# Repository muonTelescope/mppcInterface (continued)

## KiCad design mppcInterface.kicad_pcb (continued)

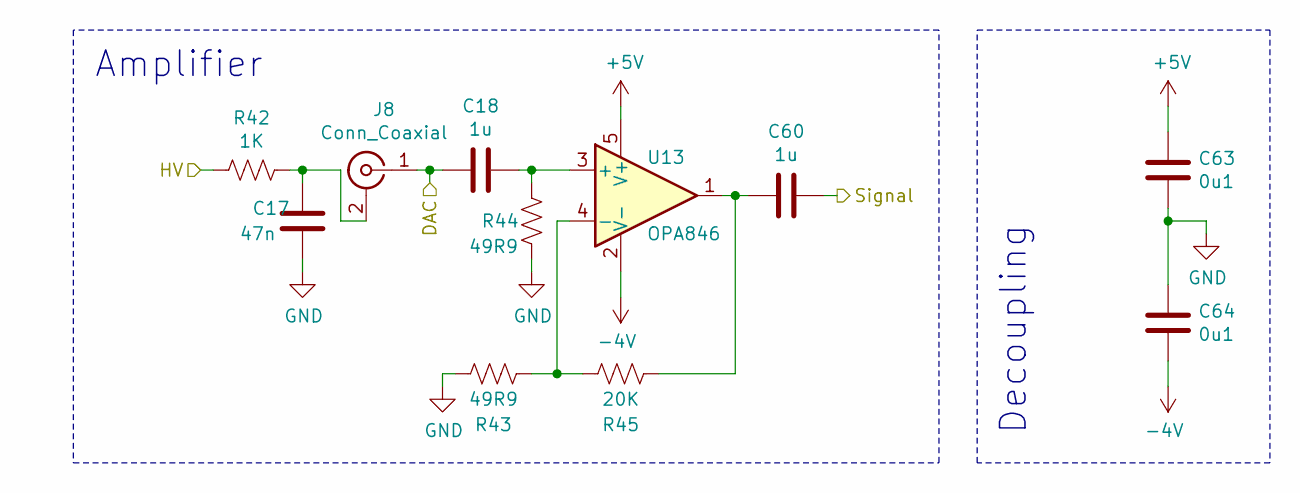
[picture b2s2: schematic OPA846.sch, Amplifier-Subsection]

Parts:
C3: 47n; C_0402_1005Metric
C4, C25: 1u; C_0402_1005Metric
C28, C29: 0u1; C_0402_1005Metric
J1: Conn_Coaxial; U.FL_Hirose_U.FL-R-SMT-1_Vertical
R7: 1K; R_0402_1005Metric
R8, R9: 49R9; R_0402_1005Metric
R10: 20K; R_0402_1005Metric
U6: OPA846; SOT-23-5

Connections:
+5V: C28.1, U6.5 (V+); also elsewhere on the board
-4V: C29.2, U6.2 (V-); also elsewhere on the board
/DAC0: C4.2, J1.1 (In); also elsewhere on the board
/HV: R7.2; also elsewhere on the board
CH0: C25.1; also elsewhere on the board
GND: C3.2, C28.2, C29.1, R8.1, R9.1; also elsewhere on the board
unnamed: C3.1, J1.2 (Ext), R7.1
unnamed: C4.1, R9.2, U6.3 (+)
unnamed: C25.2, R10.1, U6.1
unnamed: R8.2, R10.2, U6.4 (-)

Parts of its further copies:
C5, C7, C9, C11, C13, C15, C17: 47n; C_0402_1005Metric
C6, C8, C10, C12, C14, C16, C18, C30, C35, C40, C45, C50, C55, C60: 1u; C_0402_1005Metric
C33, C34, C38, C39, C43, C44, C48, C49, C53, C54, C58, C59, C63, C64: 0u1; C_0402_1005Metric
J2, J3, J4, J5, J6, J7, J8: Conn_Coaxial; U.FL_Hirose_U.FL-R-SMT-1_Vertical
R12, R17, R22, R27, R32, R37, R42: 1K; R_0402_1005Metric
R13, R14, R18, R19, R23, R24, R28, R29, R33, R34, R38, R39, R43, R44: 49R9; R_0402_1005Metric
R15, R20, R25, R30, R35, R40, R45: 20K; R_0402_1005Metric
U7, U8, U9, U10, U11, U12, U13: OPA846; SOT-23-5

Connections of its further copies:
+5V: C33.1, C38.1, C43.1, C48.1, C53.1, C58.1, C63.1, U7.5 (V+), U8.5 (V+), U9.5 (V+), U10.5 (V+), U11.5 (V+), U12.5 (V+), U13.5 (V+); also elsewhere on the board
-4V: C34.2, C39.2, C44.2, C49.2, C54.2, C59.2, C64.2, U7.2 (V-), U8.2 (V-), U9.2 (V-), U10.2 (V-), U11.2 (V-), U12.2 (V-), U13.2 (V-); also elsewhere on the board
/DAC1: C6.2, J2.1 (In); also elsewhere on the board
/DAC2: C8.2, J3.1 (In); also elsewhere on the board
/DAC3: C10.2, J4.1 (In); also elsewhere on the board
/DAC4: C12.2, J5.1 (In); also elsewhere on the board
/DAC5: C14.2, J6.1 (In); also elsewhere on the board
/DAC6: C16.2, J7.1 (In); also elsewhere on the board
/DAC7: C18.2, J8.1 (In); also elsewhere on the board
/HV: R12.2, R17.2, R22.2, R27.2, R32.2, R37.2, R42.2; also elsewhere on the board
CH1: C30.1; also elsewhere on the board
CH2: C35.1; also elsewhere on the board
CH3: C40.1; also elsewhere on the board
CH4: C45.1; also elsewhere on the board
CH5: C50.1; also elsewhere on the board
CH6: C55.1; also elsewhere on the board
CH7: C60.1; also elsewhere on the board
GND: C5.2, C7.2, C9.2, C11.2, C13.2, C15.2, C17.2, C33.2, C34.1, C38.2, C39.1, C43.2, C44.1, C48.2, C49.1, C53.2, C54.1, C58.2, C59.1, C63.2, C64.1, R13.1, R14.1, R18.1, R19.1, R23.1, R24.1, R28.1, R29.1, R33.1, R34.1, R38.1, R39.1, R43.1, R44.1; also elsewhere on the board
unnamed: C5.1, J2.2 (Ext), R12.1
unnamed: C6.1, R14.2, U7.3 (+)
unnamed: C7.1, J3.2 (Ext), R17.1
unnamed: C8.1, R19.2, U8.3 (+)
unnamed: C9.1, J4.2 (Ext), R22.1
unnamed: C10.1, R24.2, U9.3 (+)
unnamed: C11.1, J5.2 (Ext), R27.1
unnamed: C12.1, R29.2, U10.3 (+)
unnamed: C13.1, J6.2 (Ext), R32.1
unnamed: C14.1, R34.2, U11.3 (+)
unnamed: C15.1, J7.2 (Ext), R37.1
unnamed: C16.1, R39.2, U12.3 (+)
unnamed: C17.1, J8.2 (Ext), R42.1
unnamed: C18.1, R44.2, U13.3 (+)
unnamed: C30.2, R15.1, U7.1
unnamed: C35.2, R20.1, U8.1
unnamed: C40.2, R25.1, U9.1
unnamed: C45.2, R30.1, U10.1
unnamed: C50.2, R35.1, U11.1
unnamed: C55.2, R40.1, U12.1
unnamed: C60.2, R45.1, U13.1
unnamed: R13.2, R15.2, U7.4 (-)
unnamed: R18.2, R20.2, U8.4 (-)
unnamed: R23.2, R25.2, U9.4 (-)
unnamed: R28.2, R30.2, U10.4 (-)
unnamed: R33.2, R35.2, U11.4 (-)
unnamed: R38.2, R40.2, U12.4 (-)
unnamed: R43.2, R45.2, U13.4 (-)

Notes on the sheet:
Decoupling
Amplifier

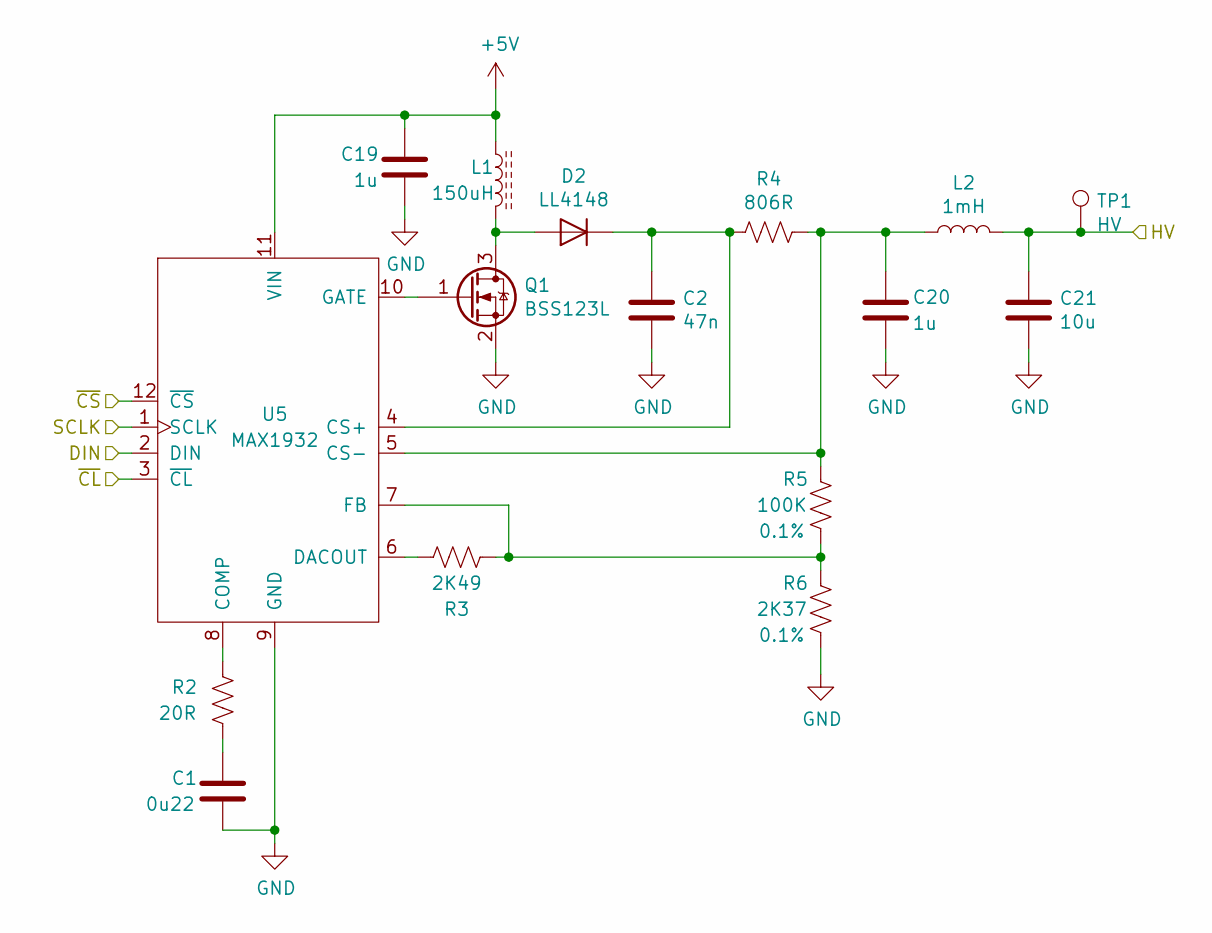
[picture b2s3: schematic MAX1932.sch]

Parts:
C1: 0u22; C_0402_1005Metric
C2: 47n; C_1206_3216Metric
C19: 1u; C_0805_2012Metric
C20: 1u; C_1206_3216Metric
C21: 10u; C_2220_5650Metric
D2: LL4148; D_MiniMELF
L1: 150uH; SRN4018
L2: 1mH; L_1210_3225Metric
Q1: BSS123L; SOT-23
R2: 20R; R_0402_1005Metric
R3: 2K49; R_0402_1005Metric
R4: 806R; R_0402_1005Metric
R5: 100K; R_0402_1005Metric; Tolerance 0.1%
R6: 2K37; R_0402_1005Metric; Tolerance 0.1%
TP1: HV; TestPoint_Bridge_Pitch2.0mm_Drill0.7mm
U5: MAX1932; TQFN-12

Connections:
+5V: C19.1, L1.1, U5.11 (VIN); also elsewhere on the board
/HV: C21.1, L2.2, TP1.1; also elsewhere on the board
CL: U5.3 (~CL)
GND: C1.2, C2.2, C19.2, C20.2, C21.2, Q1.2 (S), R6.2, U5.9 (GND); also elsewhere on the board
HV_CS: U5.12 (~CS); also elsewhere on the board
MOSI: U5.2 (DIN); also elsewhere on the board
unnamed: C1.1, R2.2
unnamed: C2.1, D2.1 (K), R4.2, U5.4 (CS+)
unnamed: C20.1, L2.1, R4.1, R5.1, U5.5 (CS-)
unnamed: D2.2 (A), L1.2, Q1.3 (D)
unnamed: Q1.1 (G), U5.10 (GATE)
unnamed: R2.1, U5.8 (COMP)
unnamed: R3.1, R5.2, R6.1, U5.7 (FB)
unnamed: R3.2, U5.6 (DACOUT)
SCLK: U5.1 (SCLK); also elsewhere on the board

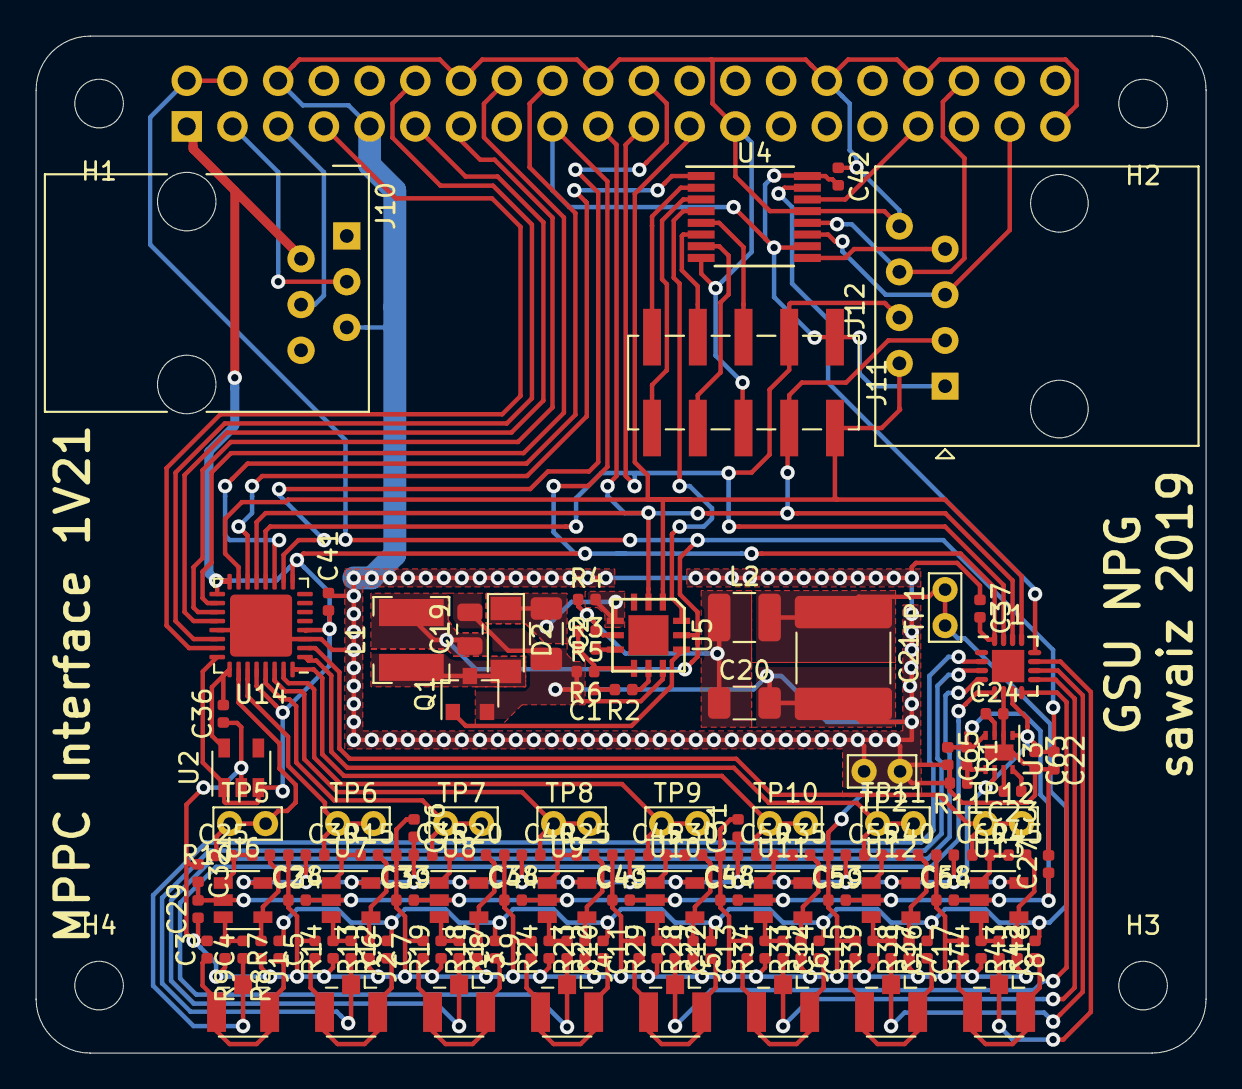
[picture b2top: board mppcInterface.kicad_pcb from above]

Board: 2 copper layers, 65.0 x 56.5 mm, 140 parts (1 on the bottom side), 90 nets.

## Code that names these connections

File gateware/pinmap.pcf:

# example.pcf

# Channels as inputs

set_io --warn-no-port CH0 31
set_io --warn-no-port CH1 32
set_io --warn-no-port CH2 1
set_io --warn-no-port CH3 2
set_io --warn-no-port CH4 20
set_io --warn-no-port CH5 22
set_io --warn-no-port CH6 23
set_io --warn-no-port CH7 26

set_io --warn-no-port LED0 30
set_io --warn-no-port LED1 29
set_io --warn-no-port LED2 27

# Output to Pi

set_io --warn-no-port gpioSDO 13 # Pin 13 is SDI on FPGA -> Pin 19, GPIO10, WiringPi 12, MOSI on RaspberryPi
set_io --warn-no-port gpioSDI 12 # Pin 12 is SDO on FPGA -> Pin 21, GPIO09, WiringPi 13, MISO on RaspberryPi
set_io --warn-no-port gpioSCK 15 # Pin 15 is SCK on FPGA -> Pin 23, GPIO11, WiringPi 14, SCK  on RaspberryPi
set_io --warn-no-port gpioSS  14 # Pin 14 is SS  on FPGA -> Pin 18, GPIO24, WiringPi 05, SS   on RaspberryPi

set_io --warn-no-port CLK     6  # Pin 6  on FPGA -> Pin 07, GPIO4, WiringPi 07, CLK on RaspberryPi

set_io --warn-no-port gpio18  7  # Pin 07 on FPGA -> Pin 12, GPIO18, WiringPi 01 on RaspberryPi 
set_io --warn-no-port gpio17  5  # Pin 05 on FPGA -> Pin 11, GPIO17, WiringPi 00 on RaspberryPi
set_io --warn-no-port gpio23  19 # Pin 19 on FPGA -> Pin 16, GPIO23, WiringPi 04 on RaspberryPi
set_io --warn-no-port gpio27  8  # Pin 08 on FPGA -> Pin 13, GPIO27, WiringPi 02 on RaspberryPi

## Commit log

2016-03-27 Copied over from other repo
2016-03-27 fdsfs
2016-04-06 Cad model Built
2016-04-22 Code has website and nodejs gpio control
2016-04-23 Website is coming along, code looks a lot better
2016-05-19 Removed code directory
2016-06-28 Changed to channel modules, still need a uC on board
2016-06-28 Schematic Changes
2016-06-29 Modules, Eth jack, and uC in place
2016-06-30 New step files, board outline added
2016-07-01 New Design
2016-07-05 updated assembly
2016-07-05 added 403C part
2016-07-05 Stuff
2016-07-05 Jonathan Doesnt Know How To Linux
2016-07-05 Routed Interface
2016-07-05 More Traces
2016-07-06 Arduino Traces Started
2016-07-06 Finished Traces
2016-07-06 Power and GND to board out
2016-07-07 Copper Pours and step/decal files
2016-07-07 Fixed Switch
2016-07-07 master slave traces
2016-07-08 Removing showcase files
2016-07-08 Added proper Readme
2016-07-08 Updated Submodule
2016-07-08 Change links to local refrences
2016-07-08 Updated BOM
2016-07-11 Added desktop.ini to gitIgnore
2016-07-12 updated assemblies
2016-07-12 updated decal
2016-07-12 updated board
2016-07-12 added I2C traces
2016-07-18 changed board
2016-07-19 updated renderings
2016-07-21 changed renderings
2016-07-21 changed a rendering
2016-07-22 Finished routing board
2016-07-25 Finished Board
2016-07-25 fixed board hole
2016-07-25 board thickness
2016-07-25 created 4 channel assembly
2016-07-25 Fixed BOM
2016-07-25 added pictures
2016-07-29 readme change
2016-07-29 added direct signal traces
2016-08-03 updated parts
2016-08-08 updated with new HV Boards
2016-08-09 added standoffs and updated assembly
2016-08-26 Updated Board for new voltage inverter and I2C LLC
2016-09-30 Updated version and renamed
2016-10-04 Renaming
2016-10-06 Ground plane fixes
2016-10-13 Smaller board, more compact routing
2016-10-13 Coincidence left
2016-10-17 Neg supply built
2016-10-18 Boad completed ready for review
2016-10-19 Cad completed, needs logo, name, and accelerometer
2016-10-19 Added logos, accelerometer, name, etc
2016-10-19 Replaced decals
2016-10-24 Added grounding pads, test pounts, fixed arduino master i2c swap
2016-10-25 marked V2, cad layout still left, uploaded to oshpark
2017-01-07 Updated to 2017 inventor files, redid renders,updated submodule
2017-06-09 Changed surface mount pads to surface mount female headders, changed year to 2017
2019-01-06 New year, new branch, new design, new EDA tool. Readme to be updated soon
2019-01-06 Removed submodule file
2019-01-06 renamef from HV
2019-01-12 Max1932 routed, fpga signal in router. Going to removed Voltage div here
2019-01-12 -5v supply, fpga routed
2019-01-12 routing only PI side left
2019-08-13 Wired up board
2019-09-20 Changed inverter IC, added some decoupling
2019-09-20 Removed bak files
2019-10-23 Finsihed layout for 1v2
2019-10-23 Added more decopling, changed I2C jack to be compatible with 6P4C
2020-08-21 Initial update to 1.3
2021-01-27 updated readme a bit
2021-05-03 Updating gateware
2021-05-03 Updating gatewre
2021-05-07 Gateware progress
2021-05-09 Added UART
2021-06-22 Updated gateware
2022-08-17 uart MUX
2022-08-19 Modified setup procedure, writitng docs
2022-08-20 Fixed makefiles, added more setup script
2022-08-20 Few more setup fixes, trial 3
2022-10-11 DAC working
